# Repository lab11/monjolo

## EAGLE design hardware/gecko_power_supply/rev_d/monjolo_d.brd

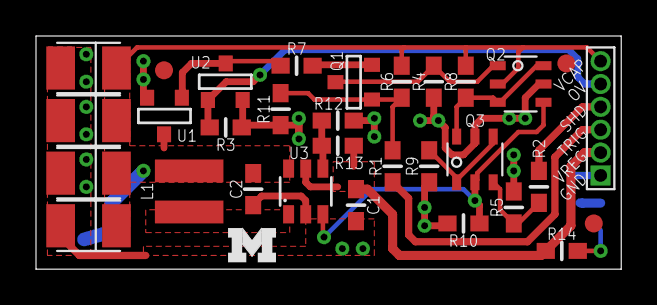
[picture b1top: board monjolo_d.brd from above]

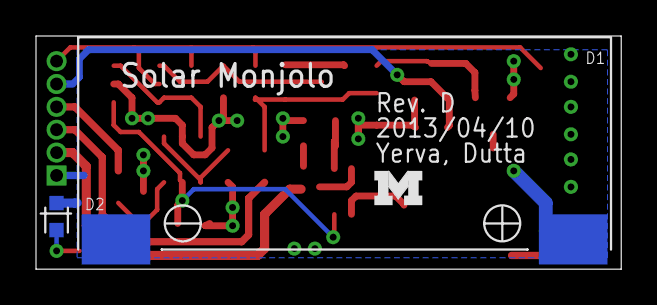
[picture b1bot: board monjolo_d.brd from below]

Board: 2 copper layers, 32.5 x 13.0 mm, 35 parts (3 on the bottom side), 17 nets.

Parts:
C1: 10uF; R0603B
C2: 4.7uF; R0603B
C3, C4, C5, C6: 100uF; CAP1210
D1: AM-1437
D2: LED-0603
JP1: HD6
JP2, JP3, JP4: FIDUCIAL1X2; FIDUCIAL-1X2
L1: 4.7uH; L2828
Q1: SOT-23
Q2, Q3: DUAL_MOSFET_NP; TSOP-6
R1, R2, R3: 1K; R0603B
R4, R5, R7, R11: 100K; R0603B
R6: 100K (DNP); R0603B
R8, R9, R10: 470K; R0603B
R12: 649K; R0603B
R13: 976K; R0603B
R14: 470; R0603B
U1: MN1382S 2.0V; MINI-3DC
U2: TC54VC 2.9V; MINI-3DC
U3: MCP1640T; SOT-23-6
U$1, U$3: UMICH_SOLID_SMALL; UMICH_SOLID_75MIL

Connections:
GND: C1.2, C2.2, C3.ANODE, C4.ANODE, C5.ANODE, C6.ANODE, D1.-, D2.C, JP1.1, Q2.5, Q3.5, R3.2, R4.2, R5.2, R9.2, R10.2, R11.2, R12.2, U1.2, U2.2, U3.2
unnamed: R12.1, R13.2, U3.4
unnamed: Q1.2, R7.2
unnamed: JP1.3, R1.1
unnamed: L1.2, U3.1
unnamed: D2.A, R14.2
unnamed: Q3.1, Q3.4, R9.1
unnamed: Q1.1, Q2.1, R4.1
unnamed: JP1.4, R2.1
unnamed: Q2.3, Q2.6, Q3.6, R8.2
unnamed: Q3.3, R2.2, R5.1
unnamed: JP1.5, R3.1, U2.1
unnamed: R7.1, U1.1, U2.3
unnamed: Q1.3, R1.2, R6.2, R11.1
unnamed: Q2.4, Q3.2, R10.1, U3.3
VCAP: C2.1, C3.CATHODE, C4.CATHODE, C5.CATHODE, C6.CATHODE, D1.+, JP1.6, L1.1, Q2.2, R6.1, R8.1, U1.3, U3.6
VREG: C1.1, JP1.2, R13.1, R14.1, U3.5

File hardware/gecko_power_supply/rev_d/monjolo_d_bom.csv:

# Bill of Materials
# Converted from monjolo_d_bom.xls
# Generated by bom_to_text.py

Qty,Value,Layout,Parts,Digikey Part #,Coilcraft,Discription,Notes
1,10uF,C0603,C1,445-7486-6-ND,,CAP CER 10UF 10V 10% X5R 0603,
1,4.7uF,C0603,C2,490-3297-6-ND,,CAP CER 4.7UF 6.3V 10% X5R 0603,
4,100uF,C1206,"C3, C4, C5, C6",478-3130-1-ND,,CAP TANT 100UF 6.3V 20% 1210,
1,AM-1437,Solar cell,D1,,,,Customer supplied.
1,LED,LED0603,D2,160-1837-6-ND,,LED BLUE CLEAR 0603 SMD,
1,4.7uH,L-US,L1,,EPL3012-472MLB,4.7 UH INDUCTOR,
1,PMOS,SOT23-3,Q1,SI2305ADS-T1-GE3DKR-ND,,MOSFET P-CH 8V 5.4A SOT23-3,
2,MOSFET NP-CH,6-TSOP,"Q2, Q3",SI3585DV-T1-E3DKR-ND,,MOSFET N/P-CH 20V 2A/1.5A 6-TSOP,
3,1K,R0603,"R1, R2, R3",RHM1.00KCFDKR-ND,,RES 1.00K OHM 1/10W 1% 0603 SMD,
4,100K,R0603,"R4, R5, R7, R11",RHM100KCFDKR-ND,,RES 100K OHM 1/10W 1% 0603 SMD,
DNP,100K,R0603,R6,RHM100KCFDKR-ND,,RES 100K OHM 1/10W 1% 0603 SMD,To use External Trigger solder R6 instead of R11
3,470K,R0603,"R8, R9, R10",RHM470KHDKR-ND,,RES 470K OHM 1/10W 1% 0603 SMD,
1,649K,R0603,R12,541-649KHDKR-ND,,RES 649K OHM 1/10W 1% 0603 SMD,
1,976K,R0603,R13,541-976KHDKR-ND,,RES 976K OHM 1/10W 1% 0603 SMD,
1,470,R0603,R14,RHM470CFDKR-ND,,RES 470 OHM 1/10W 1% 0603 SMD,
1,MN1382S 2.0V,SOT23-3,U1,TC54VC2102ECB713DKR-ND,,IC VOLT DETECT 2.0V CMOS SMD,
1,TC54VC 2.9V,SOT23-3,U2,TC54VC2902ECB71DKR-ND,,IC VOLT DETECTOR 2.9V SOT23A,Not needed if not using external Trigger (R11 soldered)
1,MCP1640T,SOT23-6,U3,MCP1640T-I/CHYDKR-ND,,IC BOOST SYNC ADJ 0.1A SOT23-6,

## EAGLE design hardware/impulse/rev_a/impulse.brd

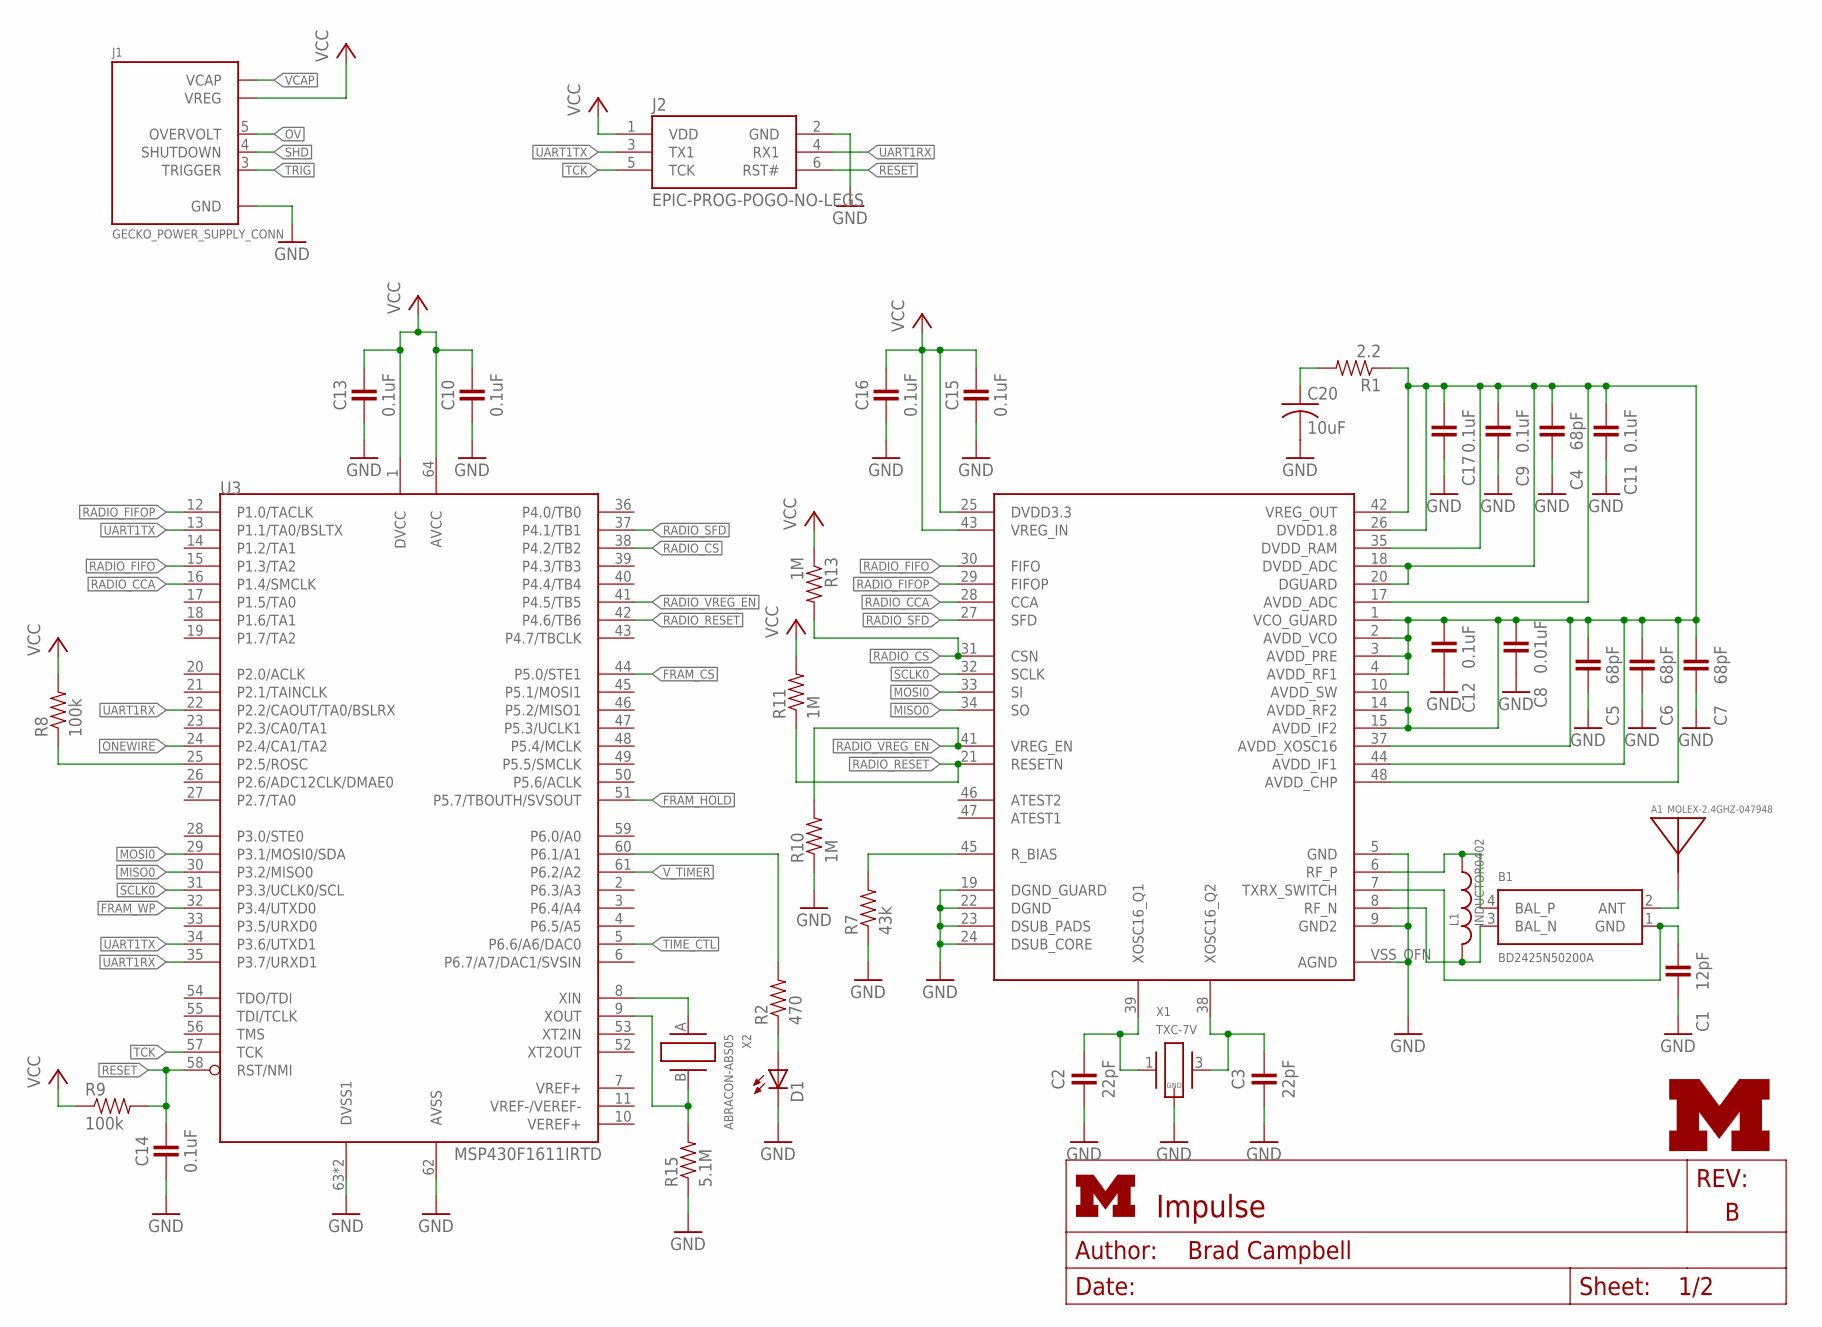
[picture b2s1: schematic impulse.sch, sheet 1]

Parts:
A1: MOLEX-2.4GHZ-047948; MOLEX-47948-ANTENNA
B1: BD2425N50200A
C1: 12pF; 0402_CAP
C2, C3: 22pF; 0402_CAP
C4, C5, C6, C7: 68pF; 0402_CAP
C8: 0.01uF; 0402_CAP
C9, C10, C11, C12, C13, C14, C15, C16, C17: 0.1uF; 0402_CAP
C20: 10uF; C0805; DIGIKEY 478-2561-1-ND
D1: LED0603; LED-0603
J1: GECKO_POWER_SUPPLY_CONN; HEADER1X6/0.05IN
J2: EPIC-PROG-POGO-NO-LEGS; TC2030-IDC-NL
L1: INDUCTOR0402; 0402_CAP; DIGIKEY 712-1419-1-ND
R1: 2.2; 0402_RES
R2: 470; 0402_RES
R7: 43k; 0402_RES
R8, R9: 100k; 0402_RES
R10, R11, R13: 1M; 0402_RES
R15: 5.1M; 0402_RES
U3: MSP430F1611IRTD; S-PVQFN-N64
U4: CC2420RGZ; S-PVQFN-N48
U$1: UMICH_SOLID_SMALL; UMICH_SOLID_75MIL
X1: TXC-7V
X2: ABRACON-ABS05; ABS05

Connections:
!FRAM_CS: U3.44 (P5.0/STE1); also elsewhere on the board
!FRAM_HOLD: U3.51 (P5.7/TBOUTH/SVSOUT); also elsewhere on the board
!FRAM_WP: U3.32 (P3.4/UTXD0); also elsewhere on the board
!RADIO_CS: R13.2, U3.38 (P4.2/TB2), U4.31 (CSN)
!RADIO_RESET: R11.1, U3.42 (P4.6/TB6), U4.21 (RESETN)
!RESET: C14.1, J2.6 (RST#), R9.2, U3.58 (RST/NMI)
GND: C1.2, C2.2, C3.2, C4.2, C5.2, C6.2, C7.2, C8.2, C9.2, C10.2, C11.2, C12.2, C13.2, C14.2, C15.2, C16.2, C17.2, C20.2, D1.C, J1.1 (GND), J2.2 (GND), R7.1, R10.1, R15.1, U3.62 (AVSS), U3.63 (DVSS1), U3.GND (DVSS1), U4.5 (GND), U4.9 (GND2), U4.19 (DGND_GUARD), U4.22 (DGND), U4.23 (DSUB_PADS), U4.24 (DSUB_CORE), U4.VSS_QFN (AGND), X1.2 (GND), X1.4 (GND); also elsewhere on the board
MISO0: U3.30 (P3.2/MISO0), U4.34 (SO); also elsewhere on the board
MOSI0: U3.29 (P3.1/MOSI0/SDA), U4.33 (SI); also elsewhere on the board
unnamed: R8.1, U3.25 (P2.5/ROSC)
unnamed: R7.2, U4.45 (R_BIAS)
unnamed: D1.A, R2.1
unnamed: C20.1, R1.2
unnamed: C4.1, C5.1, C6.1, C7.1, C8.1, C9.1, C11.1, C12.1, C17.1, R1.1, U4.1 (VCO_GUARD), U4.2 (AVDD_VCO), U4.3 (AVDD_PRE), U4.4 (AVDD_RF1), U4.10 (AVDD_SW), U4.14 (AVDD_RF2), U4.15 (AVDD_IF2), U4.17 (AVDD_ADC), U4.18 (DVDD_ADC), U4.20 (DGUARD), U4.26 (DVDD1.8), U4.35 (DVDD_RAM), U4.37 (AVDD_XOSC16), U4.42 (VREG_OUT), U4.44 (AVDD_IF1), U4.48 (AVDD_CHP)
unnamed: R2.2, U3.60 (P6.1/A1)
unnamed: B1.1 (GND), C1.1, U4.7 (TXRX_SWITCH)
unnamed: B1.3 (BAL_N), L1.2, U4.8 (RF_N)
unnamed: B1.4 (BAL_P), L1.1, U4.6 (RF_P)
unnamed: C3.1, U4.38 (XOSC16_Q2), X1.3 (2)
unnamed: C2.1, U4.39 (XOSC16_Q1), X1.1
unnamed: R15.2, U3.9 (XOUT), X2.B (2)
unnamed: U3.8 (XIN), X2.A (1)
ONEWIRE: U3.24 (P2.4/CA1/TA2); also elsewhere on the board
OV: J1.5 (OVERVOLT)
RADIO_CCA: U3.16 (P1.4/SMCLK), U4.28 (CCA)
RADIO_FIFO: U3.15 (P1.3/TA2), U4.30 (FIFO)
RADIO_FIFOP: U3.12 (P1.0/TACLK), U4.29 (FIFOP)
RADIO_SFD: U3.37 (P4.1/TB1), U4.27 (SFD)
RADIO_VREG_EN: R10.2, U3.41 (P4.5/TB5), U4.41 (VREG_EN)
SCLK0: U3.31 (P3.3/UCLK0/SCL), U4.32 (SCLK); also elsewhere on the board
SHD: J1.4 (SHUTDOWN)
TCK: J2.5 (TCK), U3.57 (TCK)
TIME_CTL: U3.5 (P6.6/A6/DAC0); also elsewhere on the board
TRIG: J1.3 (TRIGGER)
UART1RX: J2.4 (RX1), U3.22 (P2.2/CAOUT/TA0/BSLRX), U3.35 (P3.7/URXD1)
UART1TX: J2.3 (TX1), U3.13 (P1.1/TA0/BSLTX), U3.34 (P3.6/UTXD1)
UNBAL: A1.1, B1.2 (ANT)
VCAP: J1.6 (VCAP)
VCC: C10.1, C13.1, C15.1, C16.1, J1.2 (VREG), J2.1 (VDD), R8.2, R9.1, R11.2, R13.1, U3.1 (DVCC), U3.64 (AVCC), U4.25 (DVDD3.3), U4.43 (VREG_IN); also elsewhere on the board
V_TIMER: U3.61 (P6.2/A2); also elsewhere on the board

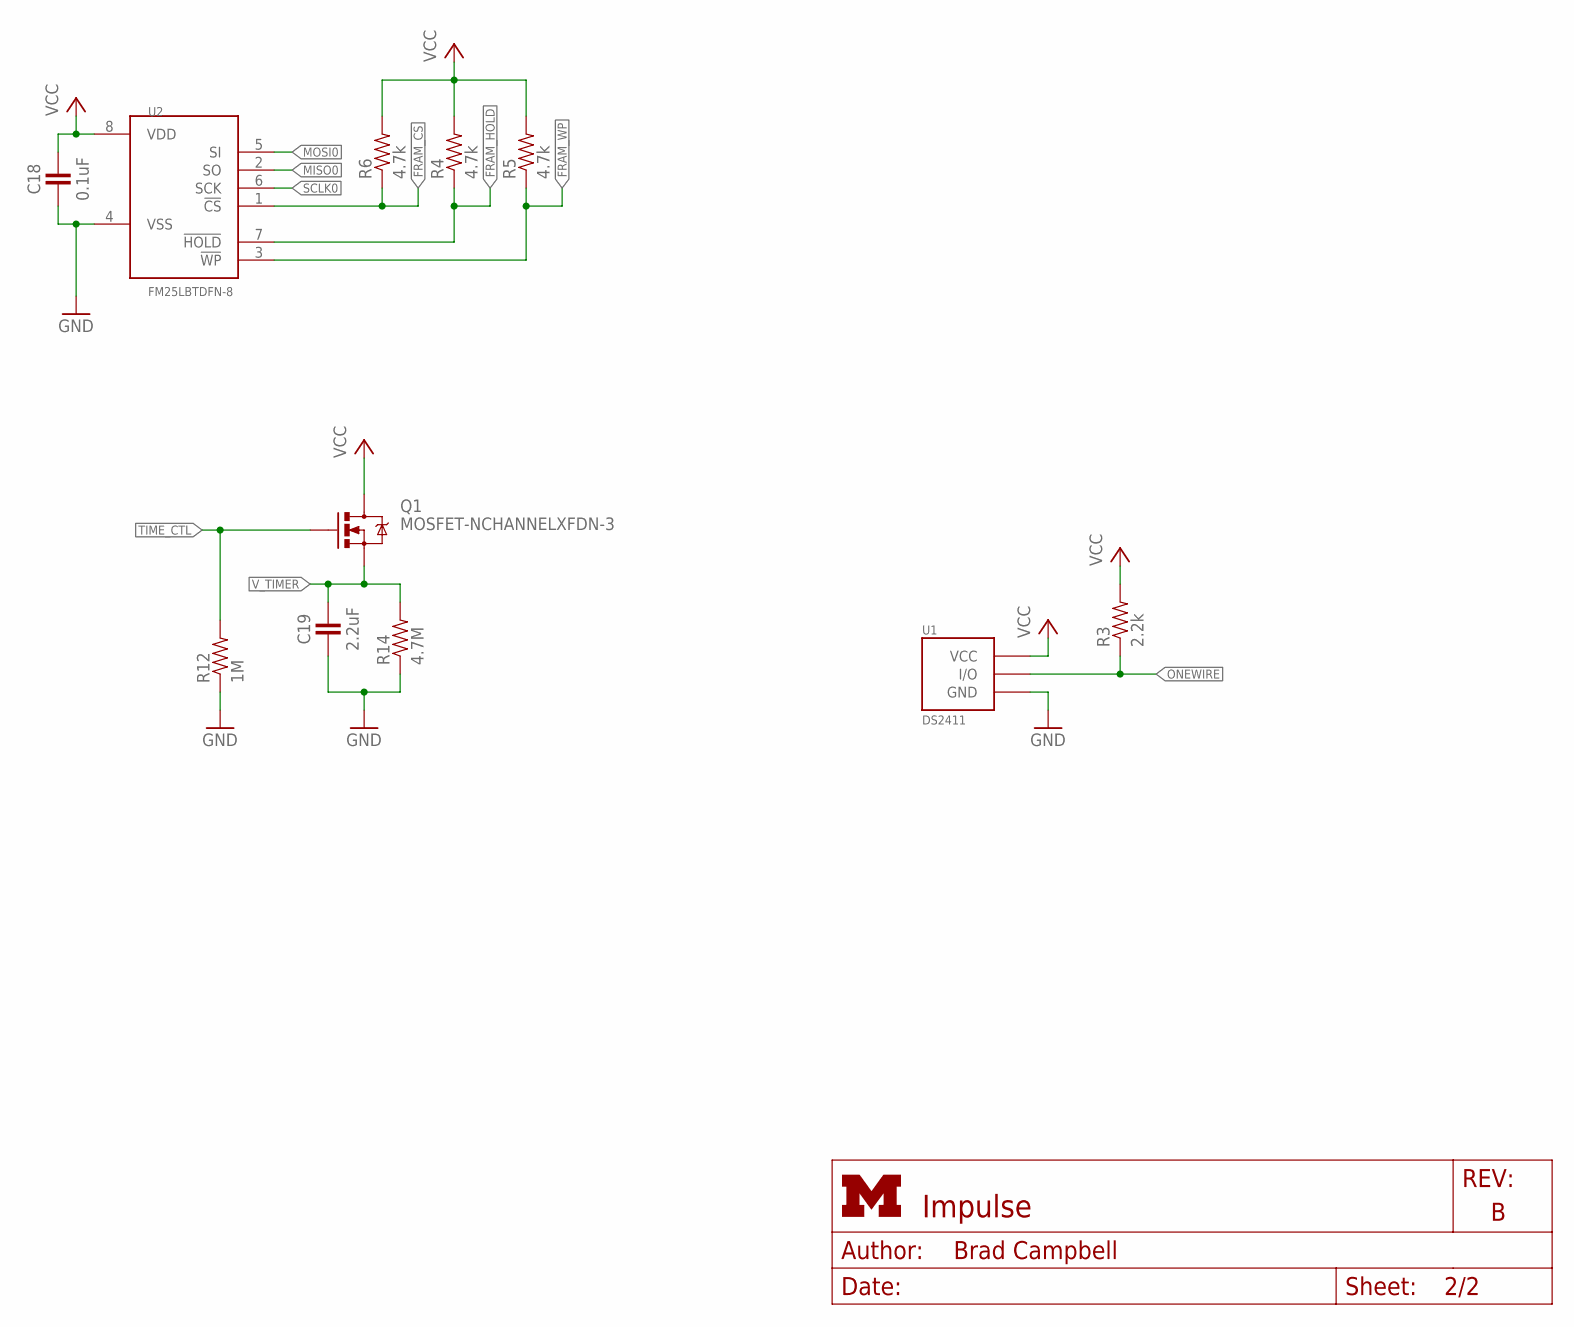
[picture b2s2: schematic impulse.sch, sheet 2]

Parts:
C18: 0.1uF; 0402_CAP
C19: 2.2uF; 0402_CAP
Q1: MOSFET-NCHANNELXFDN-3; XFDFN-3
R3: 2.2k; 0402_RES
R4, R5, R6: 4.7k; 0402_RES
R12: 1M; 0402_RES
R14: 4.7M; 0402_RES
U1: DS2411; SOT-23
U2: FM25LBTDFN-8; TDFN-8; DIGIKEY FM25L04B-DGRA-ND

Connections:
!FRAM_CS: R6.1, U2.1 (!CS); also elsewhere on the board
!FRAM_HOLD: R4.1, U2.7 (!HOLD); also elsewhere on the board
!FRAM_WP: R5.1, U2.3 (!WP); also elsewhere on the board
GND: C18.2, C19.2, R12.1, R14.1, U1.3 (GND), U2.4 (VSS); also elsewhere on the board
MISO0: U2.2 (SO); also elsewhere on the board
MOSI0: U2.5 (SI); also elsewhere on the board
ONEWIRE: R3.1, U1.1 (I/O); also elsewhere on the board
SCLK0: U2.6 (SCK); also elsewhere on the board
TIME_CTL: Q1.G, R12.2; also elsewhere on the board
VCC: C18.1, Q1.D, R3.2, R4.2, R5.2, R6.2, U1.2 (VCC), U2.8 (VDD); also elsewhere on the board
V_TIMER: C19.1, Q1.S, R14.2; also elsewhere on the board

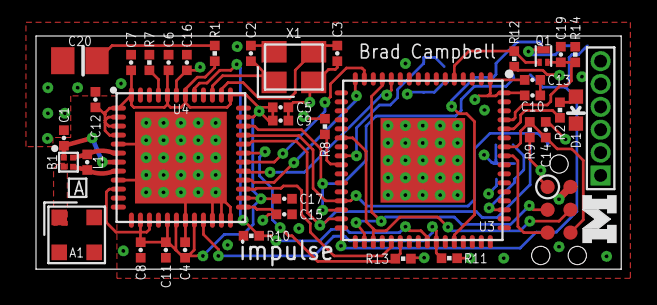
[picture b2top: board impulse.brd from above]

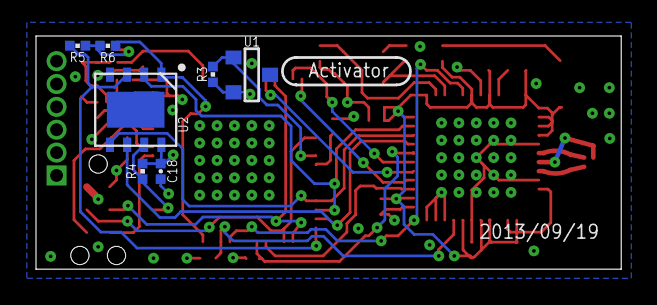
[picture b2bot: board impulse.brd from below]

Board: 4 copper layers, 32.5 x 13.0 mm, 47 parts (7 on the bottom side), 34 nets.

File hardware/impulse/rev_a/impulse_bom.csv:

# Bill of Materials
# Converted from impulse_bom.xlsx
# Generated by bom_to_text.py

Qty,Value,Device,Package,Parts,Description,DIGIKEY,MOUSER,TAG-CONNECT
1,MOLEX-2.4GHZ-047948,MOLEX-2.4GHZ-047948,MOLEX-47948-ANTENNA,A1,,WM4893CT-ND,,
1,BD2425N50200A,BD2425N50200A,BD2425N50200A,B1,,1173-1063-1-ND,,
1,12pF,CAPACITOR,0402_CAP,C1,0402 Capacitor,712-1257-1-ND,,
2,22pF,CAPACITOR,0402_CAP,"C2, C3",0402 Capacitor,445-1239-1-ND,,
4,68pF,CAPACITOR,0402_CAP,"C4, C5, C6, C7",0402 Capacitor,445-1245-1-ND,,
1,0.01uF,CAPACITOR,0402_CAP,C8,0402 Capacitor,445-1260-1-ND,,
10,0.1uF,CAPACITOR,0402_CAP,"C9, C10, C11, C12, C13, C14, C15, C16, C17, C18",0402 Capacitor,445-1265-1-ND,,
1,2.2uF,CAPACITOR,0402_CAP,C19,0402 Capacitor,445-3882-1-ND,,
1,10uF,C-USC0805,C0805,C20,"CAPACITOR, American symbol",478-2561-1-ND,,
1,,LED-0603,LED-0603,D1,LED,,,
1,GECKO_POWER_SUPPLY_CONN,GECKO_POWER_SUPPLY_CONN,HEADER1X6/0.05IN,J1,Header on the gecko power supply board.,,,
1,EPIC-PROG-POGO-NO-LEGS,EPIC-PROG-POGO-NO-LEGS,TC2030-IDC-NL,J2,Epic programmer based on the Tag Connect pogo pin cable.,,,TC2030-IDC-NL
1,INDUCTOR0402,INDUCTOR0402,0402_CAP,L1,,712-1419-1-ND,,
1,MOSFET-NCHANNELXFDN-3,MOSFET-NCHANNELXFDN-3,XFDFN-3,Q1,Generic NMOS footprint,DMN2400UFB4-7DICT-ND,,
1,2.2,RESISTOR,0402_RES,R1,Resistor,RHM2.2CECT-ND,,
1,470,RESISTOR,0402_RES,R2,Resistor,,,
1,2.2k,RESISTOR,0402_RES,R3,Resistor,RHM2.2KCECT-ND,,
3,4.7k,RESISTOR,0402_RES,"R4, R5, R6",Resistor,RHM4.7KCECT-ND,,
1,43k,RESISTOR,0402_RES,R7,Resistor,RHM43KCECT-ND,,
2,100k,RESISTOR,0402_RES,"R8, R9",Resistor,RHM100KCECT-ND,,
4,1M,RESISTOR,0402_RES,"R10, R11, R12, R13",Resistor,RHM1.0MCECT-ND,,
1,4.7M,RESISTOR,0402_RES,R14,Resistor,541-4.7MJCT-ND,,
1,DS2411,DS2411,SOT-23,U1,Maxim DS2411,DS2411R+CT-ND,,
1,FM25LBTDFN-8,FM25LBTDFN-8,TDFN-8,U2,IC FRAM 4KBIT 10MHZ 8SOIC,FM25L04B-DGRA-ND,877-FM25L04B-DG,
1,MSP430F1611IRTD,MSP430F1611IRTD,S-PVQFN-N64,U3,,296-18102-1-ND,,
1,CC2420RGZ,CC2420RGZ,S-PVQFN-N48,U4,2.4 GHz IEEE 802.15.4 / ZigBee-ready RF Transceiver,296-19585-1-ND,,
1,TXC-7V,TXC-7V,TXC-7V,X1,,887-1799-1-ND,,

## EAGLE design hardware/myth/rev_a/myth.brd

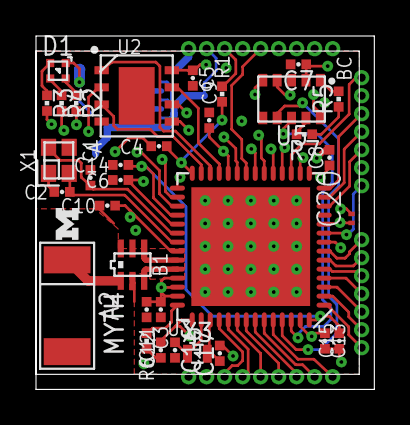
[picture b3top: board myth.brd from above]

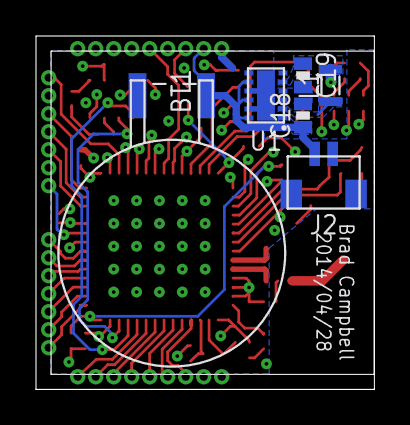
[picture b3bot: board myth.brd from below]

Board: 4 copper layers, 18.8 x 19.6 mm, 41 parts (6 on the bottom side), 55 nets.

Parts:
A2: FRACTUS-2.4GHZ-FR05-S1-N-0-102; FRACTUS-ANTENNA-FR05-S1-N-0-102
B1: 2450BM15A0002; 2450BM
BT1: ML-1220/F1AN; ML-1220/F1BN
C1, C2: 12pF; 0402_CAP
C3: 220pF; 0402_CAP
C4: 1nF; 0402_CAP
C5, C6, C8, C9, C10, C11, C12: 0.1uF; 0402_CAP
C7: 10nF; 0402_CAP
C13, C14, C15: 1uF; 0402_CAP
C16, C17: 22pF; 0402_CAP
C18, C19: 10uF; 0603_CAP
C20: 0.1uF; C0201
D1: SML-LX0404SIUPGUSB; 1MM_SQ_4PAD
J1: EPIC2-HEADER2
J2: SH_MALE_2/1MM; SH-1X2/1MM
L1: 2.2; MIPSZ201D
LOGO1: UMICH_SOLID_TINY; UMICH_SOLID_50MIL
R1: 2.2k; 0402_RES
R2, R3, R4: 1k; 0402_RES
R5, R7: 10k; 0402_RES
R6: 56k; 0402_RES
U1: TPS62740; R-PWSON-12
U2: FM25LBTDFN-8; TDFN-8
U3: CC2538; S-PVQFN-N56
U5: RV-3049-C3; MICRO-CRYSTAL-C3
X1: EPSON-FA-128; FA-128
X3: ABS05-32.768KHZ-T; ABS05

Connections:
!FRAM_CS: U2.1, U3.26
!FRAM_HOLD: U2.7, U3.25
!FRAM_WP: U2.3, U3.27
!RESET: J1.30, R1.1
!RTC_INT: U3.53, U5.7
ADC3: J1.25, U3.19
ADC4: J1.26, U3.20
ADC5: J1.27, U3.21
ADC6: J1.28, U3.22
ADC7: J1.29, U3.23
ANTENNA: A2.1, B1.1
B3: J1.9, U3.52
B4: J1.8, U3.51
B5: J1.7, U3.50
B6: J1.6, U3.49
BATTERY: BT1.POS, C18.1, J1.31, J2.2, U1.1, U1.8, U1.10, U1.12
BOOTLOADER_CTRL: J1.24, U3.18
BOOTLOADER_RX: J1.22, U3.16
BOOTLOADER_TX: J1.23, U3.17
C0: J1.21, U3.14
C1: J1.20, U3.13
C2: J1.19, U3.12
DGND_USB: J1.10, U3.1
DVDD_USB: J1.13, U3.4
GND: B1.2, B1.5, B1.6, BT1.NEG, C1.2, C2.2, C3.2, C4.2, C5.2, C6.2, C7.2, C8.2, C9.2, C10.2, C11.2, C12.2, C13.2, C14.2, C15.2, C16.2, C17.2, C18.2, C19.2, C20.2, J1.32, J2.1, R5.1, R6.2, R7.1, U1.3, U1.4, U1.9, U1.11, U1.NC, U2.4, U3.VSS_QFN, U5.6, X1.2, X1.4
I2C_SCL: J1.17, U3.9
I2C_SDA: J1.18, U3.8
LED_BLUE: R4.2, U3.30
LED_GREEN: R3.2, U3.31
LED_RED: R2.2, U3.29
unnamed: C4.1, R1.2, U3.28
unnamed: L1.1, U1.2
unnamed: C16.1, U3.44, X3.A
unnamed: D1.2, R2.1
unnamed: R6.1, U3.42
unnamed: C1.1, U3.34, X1.1
unnamed: C2.1, U3.35, X1.3
unnamed: D1.4, R3.1
unnamed: D1.3, R4.1
unnamed: C17.1, U3.45, X3.B
unnamed: R7.2, U5.9
unnamed: C14.1, C15.1, U3.32, U3.56
unnamed: R5.2, U5.1
RF_N: B1.3, U3.38
RF_P: B1.4, U3.37
RTC_CE: U3.54, U5.8
SPI_MISO: J1.14, U2.2, U3.5, U5.5
SPI_MOSI: J1.15, U2.5, U3.6, U5.10
SPI_SCK: J1.16, U2.6, U3.7, U5.4
TCK: J1.4, U3.47
TDO: J1.5, U3.48
TMS: J1.3, U3.46
USB_N: J1.12, U3.3
USB_P: J1.11, U3.2
VCC: C3.1, C5.1, C6.1, C7.1, C8.1, C9.1, C10.1, C11.1, C12.1, C13.1, C19.1, C20.1, D1.1, J1.1, L1.2, U1.5, U2.8, U3.10, U3.15, U3.24, U3.33, U3.36, U3.39, U3.40, U3.41, U3.43, U3.55, U5.2

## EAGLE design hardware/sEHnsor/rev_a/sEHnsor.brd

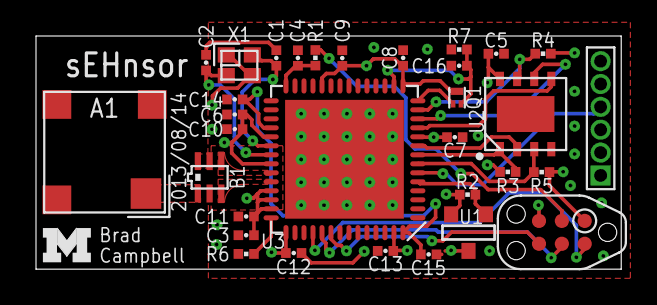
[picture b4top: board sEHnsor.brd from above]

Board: 4 copper layers, 32.5 x 13.0 mm, 33 parts (0 on the bottom side), 24 nets.

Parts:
A1: FRACTUS-2.4GHZ-FR05-S1-N-0-001; FRACTUS-ANTENNA-FR05-S1-N-0-001
B1: 2450BM15A0002; 2450BM
C1, C2: 12pF; 0402_CAP
C3: 220pF; 0402_CAP
C4: 1nF; 0402_CAP
C5, C6, C7, C8, C9, C10, C11, C12: 0.1uF; 0402_CAP
C13, C14, C15: 1uF; 0402_CAP
C16: 2.2uF; 0402_CAP
J1: GECKO_POWER_SUPPLY_CONN; HEADER1X6/0.05IN
J2: TC2030-CTX-NL; TC2030-IDC-NL
Q1: MOSFET-NCHANNELXFDN-3; XFDFN-3
R1, R2: 2.2k; 0402_RES
R3, R4, R5: 4.7k; 0402_RES
R6: 56k; 0402_RES
R7: 4.7M; 0402_RES
U1: DS2411; SOT-23
U2: FM25LBTDFN-8; TDFN-8
U3: CC2538; S-PVQFN-N56
U$1: UMICH_SOLID_SMALL; UMICH_SOLID_75MIL
X1: EPSON-FA-128; FA-128

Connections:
!FRAM_CS: R3.1, U2.1, U3.8
!FRAM_HOLD: R4.1, U2.7, U3.13
!FRAM_WP: R5.1, U2.3, U3.7
!RESET: J2.3, R1.1
ANTENNA: A1.1, B1.1
DS2411: R2.1, U1.1, U3.5
GND: B1.2, B1.5, B1.6, C1.2, C2.2, C3.2, C4.2, C5.2, C6.2, C7.2, C8.2, C9.2, C10.2, C11.2, C12.2, C13.2, C14.2, C15.2, C16.2, J1.1, J2.5, R6.2, R7.1, U1.3, U2.4, U3.VSS_QFN, X1.2, X1.4
MISO: U2.2, U3.9
MOSI: U2.5, U3.11
unnamed: C4.1, R1.2, U3.28
unnamed: R6.1, U3.42
unnamed: C1.1, U3.34, X1.1
unnamed: C2.1, U3.35, X1.3
unnamed: C14.1, C15.1, U3.32, U3.56
RF_N: B1.3, U3.38
RF_P: B1.4, U3.37
SCK: U2.6, U3.12
SHD: J1.4, U3.6
TCK: J2.4, U3.47
TDO: J2.6, U3.48
TIME_CTL: Q1.G, U3.14
TMS: J2.2, U3.46
VCC: C3.1, C5.1, C6.1, C7.1, C8.1, C9.1, C10.1, C11.1, C12.1, C13.1, J1.2, J2.1, Q1.D, R2.2, R3.2, R4.2, R5.2, U1.2, U2.8, U3.10, U3.15, U3.24, U3.33, U3.36, U3.39, U3.40, U3.41, U3.43, U3.55
V_TIMER: C16.1, Q1.S, R7.2, U3.16

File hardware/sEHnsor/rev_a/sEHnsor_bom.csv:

# Bill of Materials
# Converted from sEHnsor_bom.xlsx
# Generated by bom_to_text.py

Qty,Value,Device,Package,Parts,Description,DIGIKEY,MOUSER,NEWARK,RICHARDSON_RFPD
1,FRACTUS-2.4GHZ-FR05-S1-N-0-001,FRACTUS-2.4GHZ-FR05-S1-N-0-001,FRACTUS-ANTENNA-FR05-S1-N-0-001,A1,Fractus Reach Xtend,,,,FR05-S1-N-0001B
1,2450BM15A0002,2450BM15A0002,2450BM,B1,BALUN JTI MATCHED ZIGBEE,712-1536-1-ND,,,
2,12pF,CAPACITOR,0402_CAP,"C1, C2",0402 Capacitor,445-1236-1-ND,,,
1,220pF,CAPACITOR,0402_CAP,C3,0402 Capacitor,445-1251-1-ND,,,
1,1nF,CAPACITOR,0402_CAP,C4,0402 Capacitor,445-2651-1-ND,,,
8,0.1uF,CAPACITOR,0402_CAP,"C5, C6, C7, C8, C9, C10, C11, C12",0402 Capacitor,445-1265-1-ND,,,
3,1uF,CAPACITOR,0402_CAP,"C13, C14, C15",0402 Capacitor,445-4998-1-ND,,,
1,2.2uF,CAPACITOR,0402_CAP,C16,0402 Capacitor,445-10882-1-ND,,,
1,GECKO_POWER_SUPPLY_CONN,GECKO_POWER_SUPPLY_CONN,HEADER1X6/0.05IN,J1,Header on the gecko power supply board.,TMS-106-51-G-S-ND,,,
1,MOSFET-NCHANNELXFDN-3,MOSFET-NCHANNELXFDN-3,XFDFN-3,Q1,Generic NMOS footprint,DMN2400UFB4-7DICT-ND,,,
2,2.2k,RESISTOR,0402_RES,"R1, R2",Resistor,RHM2.2KCECT-ND,,,
3,4.7k,RESISTOR,0402_RES,"R3, R4, R5",Resistor,RHM4.7KCECT-ND,,,
1,56k,RESISTOR,0402_RES,R6,Resistor,RHM56KBHCT-ND,,,
1,4.7M,RESISTOR,0402_RES,R7,Resistor,541-4.7MJCT-ND,,,
1,DS2411,DS2411,SOT-23,U1,Maxim DS2411,DS2411R+CT-ND,,,
1,FM25LBTDFN-8,FM25LBTDFN-8,TDFN-8,U2,IC FRAM 4KBIT 10MHZ 8SOIC,FM25L04B-DGRA-ND,877-FM25L04B-DG,,
1,CC2538,CC2538,S-PVQFN-N56,U3,"A Powerful System-On-Chip for 2.4-GHz IEEE 802.15.4, 6LoWPAN",296-35797-1-ND,595-CC2538SF53RTQT,87W7713,
1,EPSON-FA-128,EPSON-FA-128,FA-128,X1,MHz RANGE CRYSTAL UNIT,SER3800CT-ND,732-FA128-32F20X-K3,,

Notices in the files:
parts and their libraries:
SparkFun-Aesthetics: Licensing: CC v3.0 Share-Alike You are welcome to use this library for commercial purposes.
